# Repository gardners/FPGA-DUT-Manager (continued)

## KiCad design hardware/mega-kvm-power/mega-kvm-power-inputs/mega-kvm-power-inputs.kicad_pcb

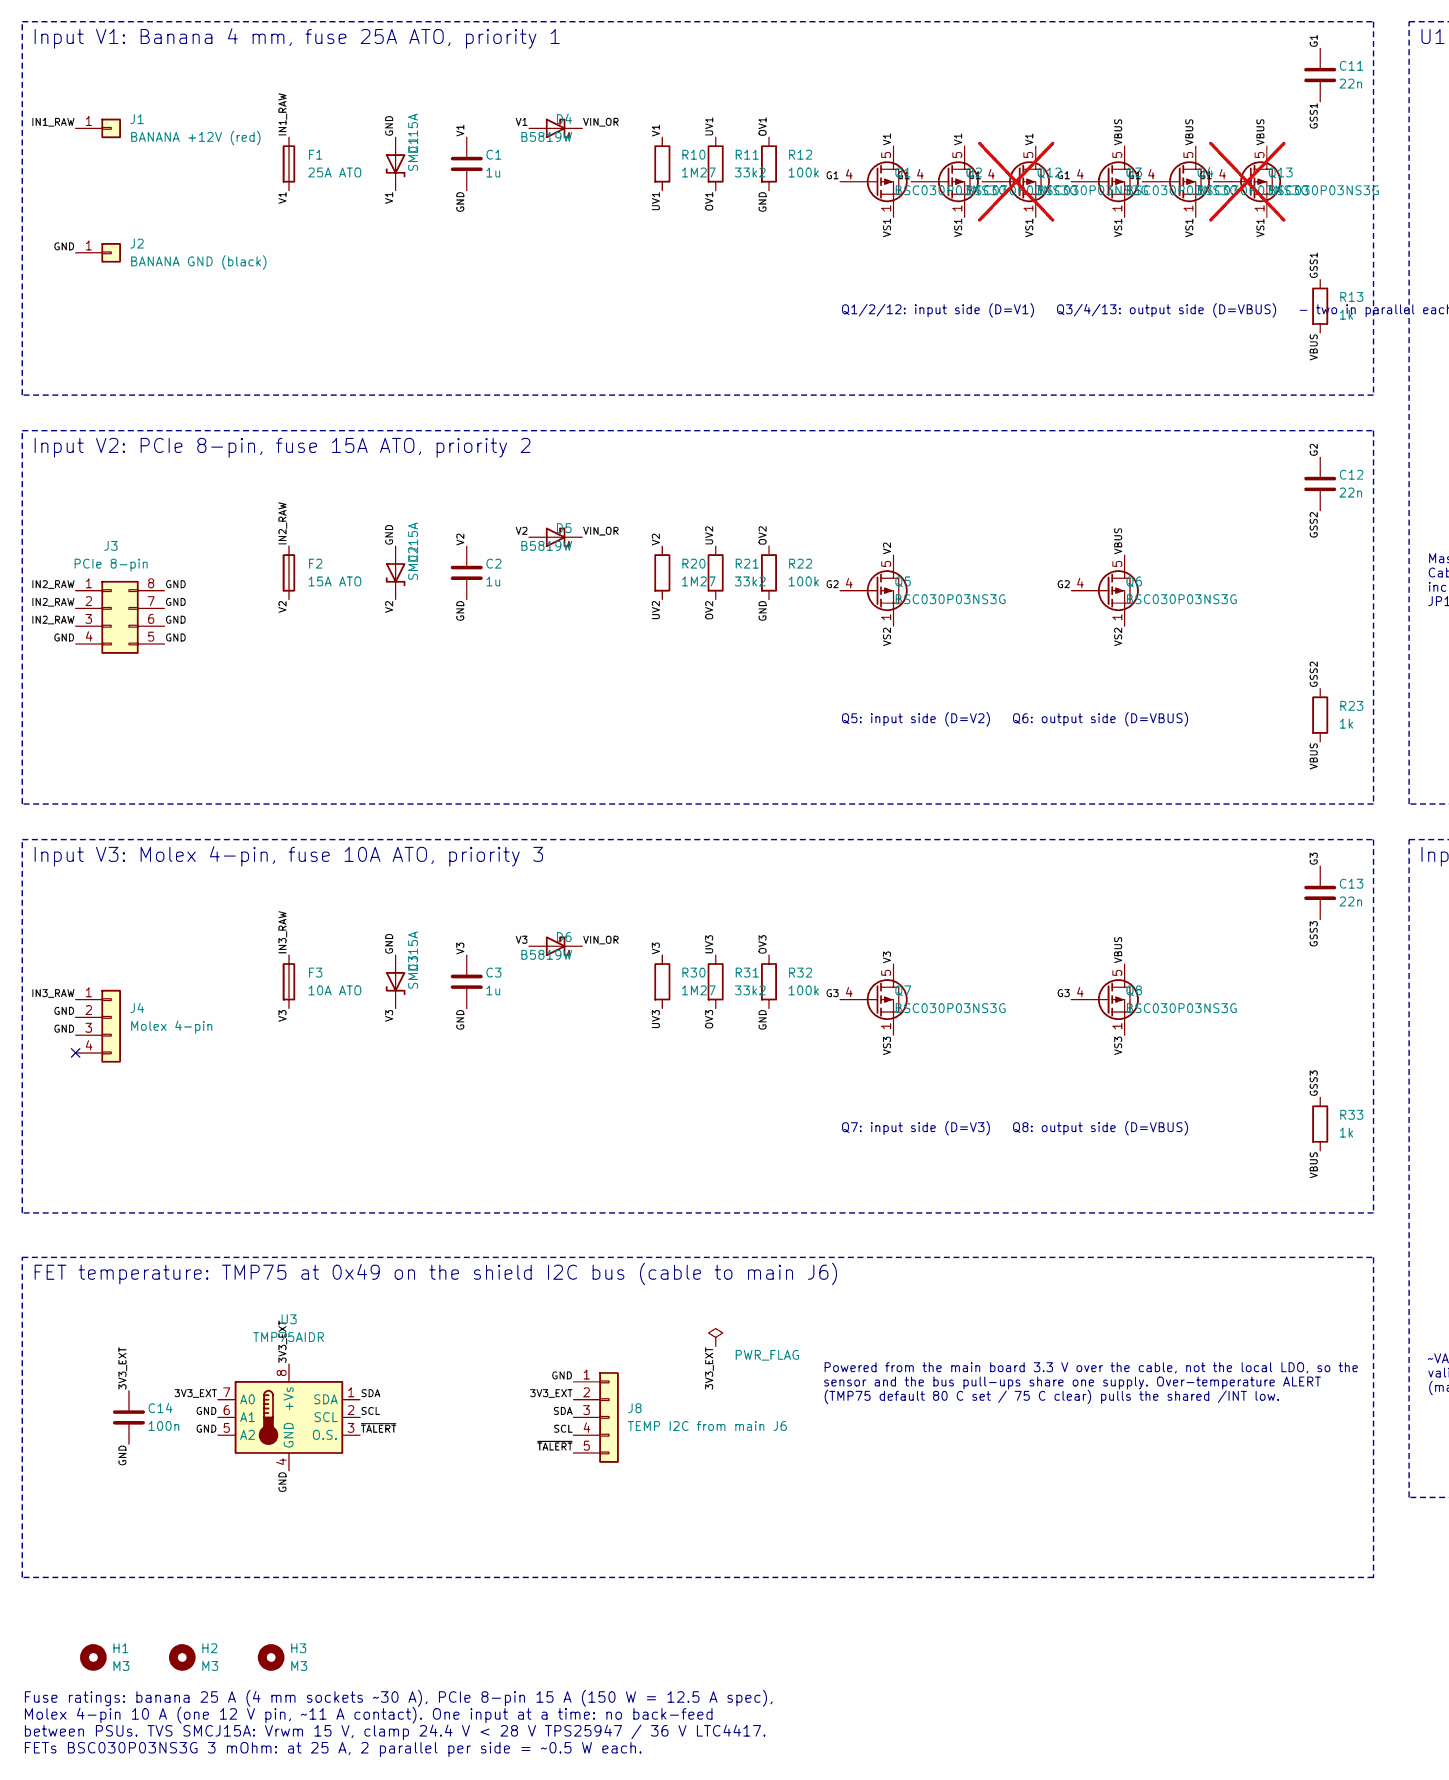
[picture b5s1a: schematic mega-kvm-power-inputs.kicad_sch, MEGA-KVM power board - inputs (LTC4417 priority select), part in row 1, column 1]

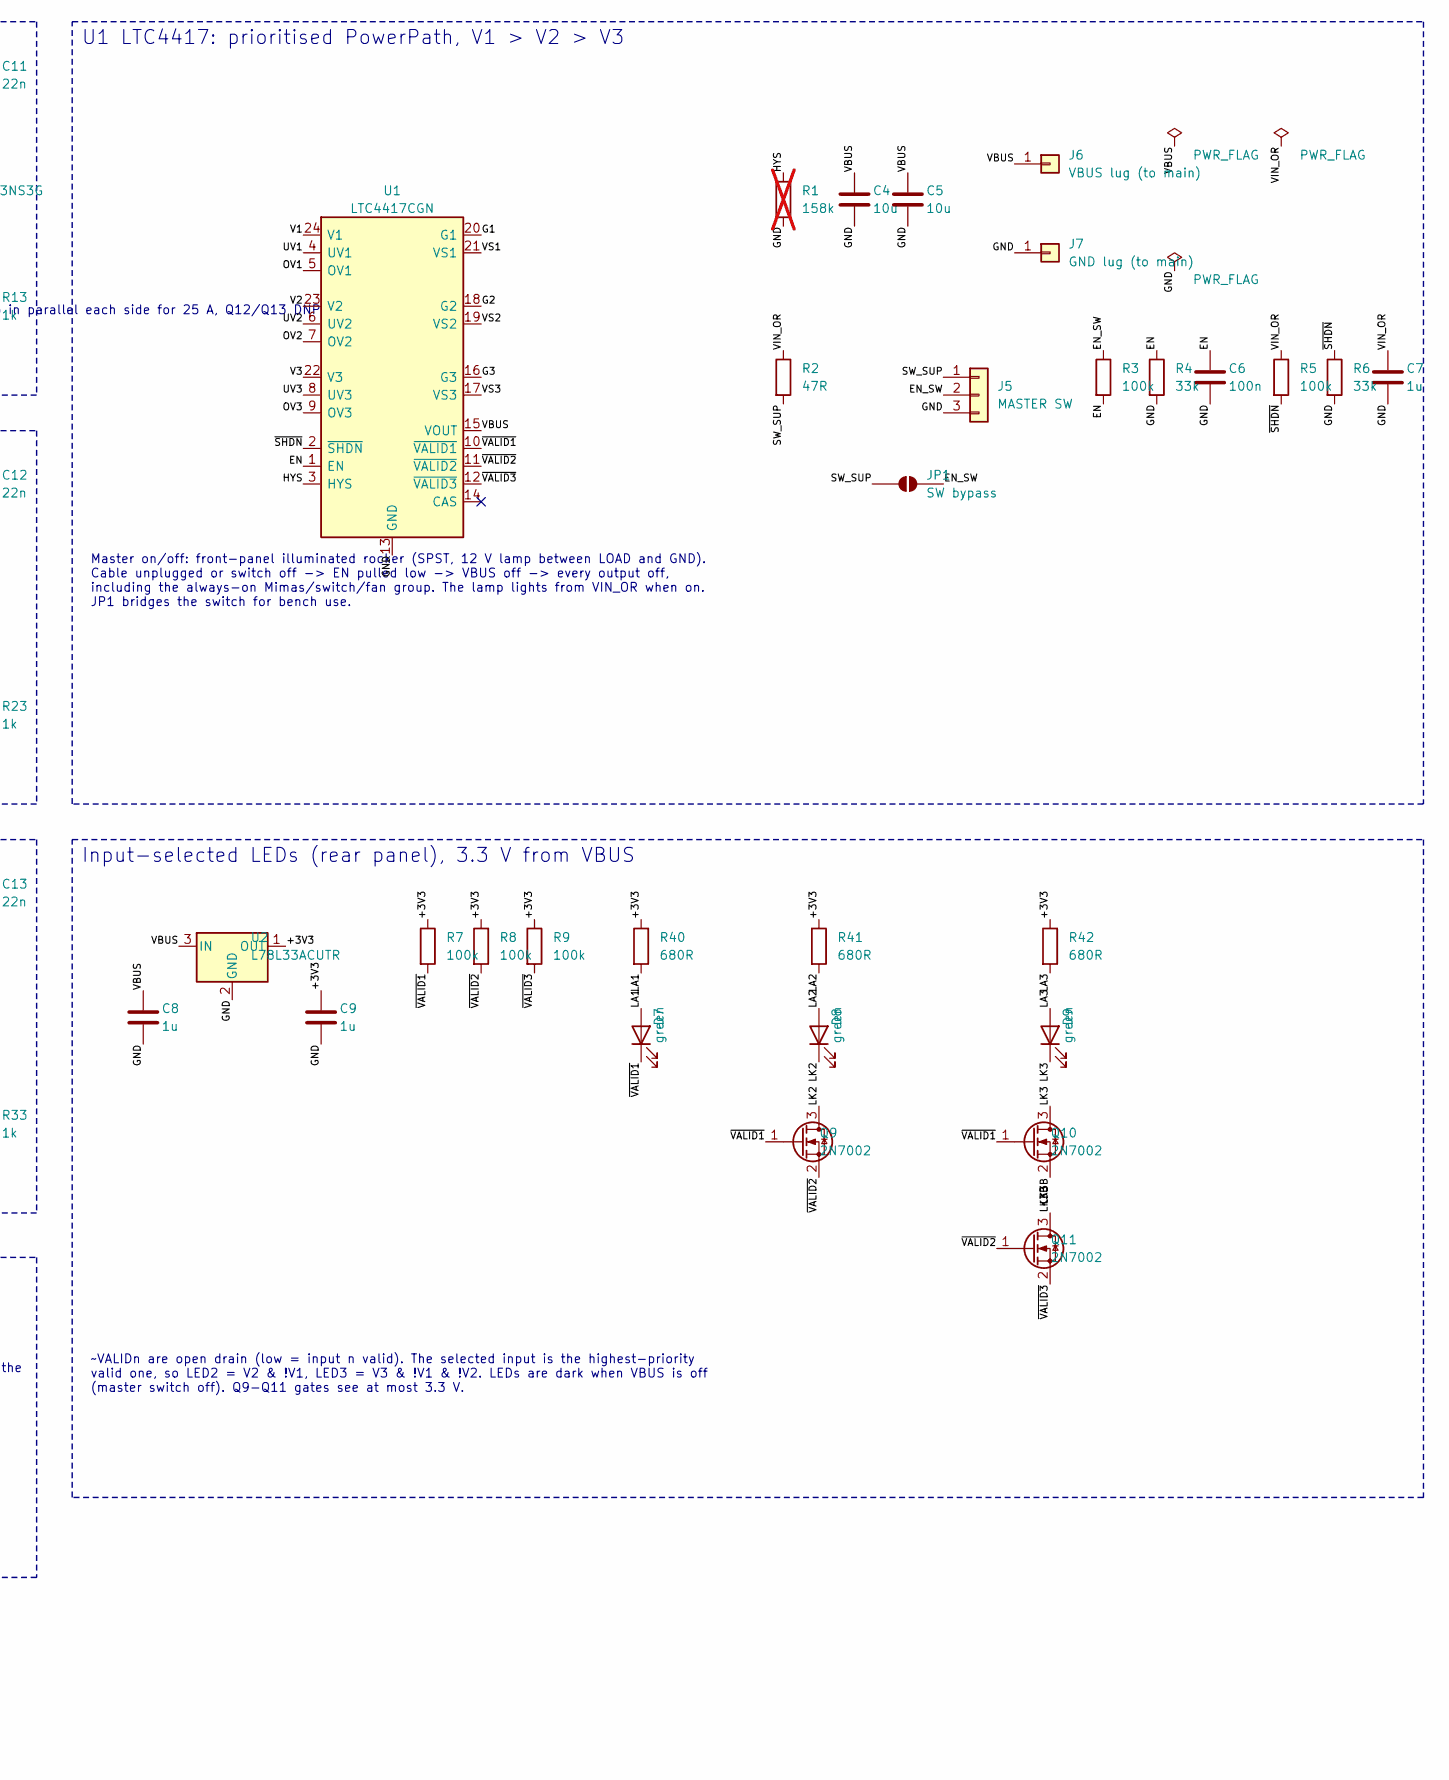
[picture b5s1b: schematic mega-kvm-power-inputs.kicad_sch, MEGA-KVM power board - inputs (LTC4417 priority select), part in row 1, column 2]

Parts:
C1, C2, C3: 1u; C_1206_3216Metric; Voltage 50V; LCSC TBD (X7R 50V)
C4, C5: 10u; C_1206_3216Metric; Voltage 25V; LCSC TBD (X7R 25V)
C6, C14: 100n; C_0603_1608Metric; Voltage 25V; LCSC C14663
C7, C8: 1u; C_0603_1608Metric; Voltage 50V; LCSC TBD (X7R 50V)
C9: 1u; C_0603_1608Metric; Voltage 16V; LCSC TBD (X7R 16V)
C11, C12, C13: 22n; C_0603_1608Metric; Voltage 50V; LCSC TBD (X7R 50V)
D1, D2, D3: SMCJ15A; D_SMC; MPN MDD SMCJ15A 1500 W, Vrwm 15 V, Vc 24.4 V; LCSC C2834490
D4, D5, D6: B5819W; D_SOD-123; MPN B5819W 40 V 1 A SOD-123; LCSC C8598
D7, D8, D9: green; LED_0603_1608Metric; LCSC TBD (0603 green, JLC basic)
F1: 25A ATO; FuseHolder_Blade_ATO_Littelfuse_FLR_178.6165; MPN Littelfuse 178.6165.0002 ATO PCB holder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; LCSC TBD / hand-fit
F2: 15A ATO; FuseHolder_Blade_ATO_Littelfuse_FLR_178.6165; MPN Littelfuse 178.6165.0002 ATO PCB holder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; LCSC TBD / hand-fit
F3: 10A ATO; FuseHolder_Blade_ATO_Littelfuse_FLR_178.6165; MPN Littelfuse 178.6165.0002 ATO PCB holder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; LCSC TBD / hand-fit
H1, H2, H3: M3; MountingHole_3.2mm_M3
J1: BANANA +12V (red); Banana_Jack_1Pin; MPN 4 mm panel socket >=30 A, red, through-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; LCSC hand-fit
J2: BANANA GND (black); Banana_Jack_1Pin; MPN 4 mm panel socket >=30 A, black; LCSC hand-fit
J3: PCIe 8-pin; Molex_Mini-Fit_Jr_5566-08A_2x04_P4.20mm_Vertical; MPN Molex Mini-Fit Jr 8-pin vertical header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; LCSC TBD / hand-fit
J4: Molex 4-pin; Molex_8981_PeripheralPower_1x04_P5.08mm_Vertical; MPN Molex 8981 4-pin male PCB header, verti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; LCSC TBD / hand-fit
J5: MASTER SW; JST_XH_B3B-XH-A_1x03_P2.50mm_Vertical; MPN JST B3B-XH-A; LCSC C144395 (verify)
J6: VBUS lug (to main); MountingHole_4.3mm_M4_Pad_Via; LCSC n/a (ring terminal + M4 screw/nut)
J7: GND lug (to main); MountingHole_4.3mm_M4_Pad_Via; LCSC n/a (ring terminal + M4 screw/nut)
J8: TEMP I2C from main J6; JST_XH_B5B-XH-A_1x05_P2.50mm_Vertical; MPN JST B5B-XH-A(LF)(SN); LCSC C157991
JP1: SW bypass; SolderJumper-2_P1.3mm_Open_RoundedPad1.0x1.5mm
Q1, Q2, Q3, Q4, Q5, Q6, Q7, Q8: BSC030P03NS3G; Infineon_PG-TDSON-8_6.15x5.15mm; MPN Infineon BSC030P03NS3G -30 V 3 mOhm; LCSC C152375
Q9, Q10, Q11: 2N7002; SOT-23; LCSC C8545
Q12, Q13: BSC030P03NS3G; Infineon_PG-TDSON-8_6.15x5.15mm; MPN Infineon BSC030P03NS3G -30 V 3 mOhm; LCSC C152375; not fitted
R1: 158k; R_0603_1608Metric; Tolerance 1%; LCSC TBD (1%, JLC basic if stocked); not fitted
R2: 47R; R_1206_3216Metric; Tolerance 1%; LCSC TBD (1%, JLC basic if stocked)
R3, R5, R7, R8, R9, R12, R22, R32: 100k; R_0603_1608Metric; Tolerance 1%; LCSC C25803
R4, R6: 33k; R_0603_1608Metric; Tolerance 1%; LCSC TBD (1%, JLC basic if stocked)
R10, R20, R30: 1M27; R_0603_1608Metric; Tolerance 1%; LCSC TBD (1%, JLC basic if stocked)
R11, R21, R31: 33k2; R_0603_1608Metric; Tolerance 1%; LCSC TBD (1%, JLC basic if stocked)
R13, R23, R33: 1k; R_0603_1608Metric; Tolerance 1%; LCSC C21190
R40, R41, R42: 680R; R_0603_1608Metric; Tolerance 1%; LCSC TBD (1%, JLC basic if stocked)
U1: LTC4417CGN; SSOP-24_3.9x8.7mm_P0.635mm; MPN ADI LTC4417CGN#PBF; LCSC C688500 (low stock: order via JLC globa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
U2: L78L33ACUTR; SOT-89-3; MPN ST L78L33ACUTR; LCSC TBD (78L33 SOT-89, 30 V in)
U3: TMP75AIDR; SOIC-8_3.9x4.9mm_P1.27mm; MPN TI TMP75AIDR (LM75 pinout, 0x48-0x4F), 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; LCSC C30389

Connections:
/3V3_EXT: C14.1, J8.2, U3.7 (A0), U3.8 (+Vs)
/+3V3: C9.1, R7.1, R8.1, R9.1, R40.1, R41.1, R42.1, U2.1 (OUT)
/EN: C6.1, R3.2, R4.1, U1.1 (EN)
/EN_SW: J5.2, JP1.2 (B), R3.1
/G1: C11.1, Q1.4 (G), Q2.4 (G), Q3.4 (G), Q4.4 (G), Q12.4 (G), Q13.4 (G), U1.20 (G1)
/G2: C12.1, Q5.4 (G), Q6.4 (G), U1.18 (G2)
/G3: C13.1, Q7.4 (G), Q8.4 (G), U1.16 (G3)
/GND: C1.2, C2.2, C3.2, C4.2, C5.2, C6.2, C7.2, C8.2, C9.2, C14.2, D1.2 (A), D2.2 (A), D3.2 (A), J2.1, J3.4, J3.5, J3.6, J3.7, J3.8, J4.2, J4.3, J5.3, J7.1, J8.1, R1.2, R4.2, R6.2, R12.2, R22.2, R32.2, U1.13 (GND), U2.2 (GND), U3.4 (GND), U3.5 (A2), U3.6 (A1)
/GSS1: C11.2, R13.1
/GSS2: C12.2, R23.1
/GSS3: C13.2, R33.1
/HYS: R1.1, U1.3 (HYS)
/IN1_RAW: F1.1, J1.1
/IN2_RAW: F2.1, J3.1, J3.2, J3.3
/IN3_RAW: F3.1, J4.1
/LA1: D7.2 (A), R40.2
/LA2: D8.2 (A), R41.2
/LA3: D9.2 (A), R42.2
/LK2: D8.1 (K), Q9.3 (D)
/LK3: D9.1 (K), Q10.3 (D)
/LK3B: Q10.2 (S), Q11.3 (D)
/OV1: R11.2, R12.1, U1.5 (OV1)
/OV2: R21.2, R22.1, U1.7 (OV2)
/OV3: R31.2, R32.1, U1.9 (OV3)
/SCL: J8.4, U3.2 (SCL)
/SDA: J8.3, U3.1 (SDA)
/SW_SUP: J5.1, JP1.1 (A), R2.2
/UV1: R10.2, R11.1, U1.4 (UV1)
/UV2: R20.2, R21.1, U1.6 (UV2)
/UV3: R30.2, R31.1, U1.8 (UV3)
/V1: C1.1, D1.1 (K), D4.2 (A), F1.2, Q1.5 (D), Q2.5 (D), Q12.5 (D), R10.1, U1.24 (V1)
/V2: C2.1, D2.1 (K), D5.2 (A), F2.2, Q5.5 (D), R20.1, U1.23 (V2)
/V3: C3.1, D3.1 (K), D6.2 (A), F3.2, Q7.5 (D), R30.1, U1.22 (V3)
/VBUS: C4.1, C5.1, C8.1, J6.1, Q3.5 (D), Q4.5 (D), Q6.5 (D), Q8.5 (D), Q13.5 (D), R13.2, R23.2, R33.2, U1.15 (VOUT), U2.3 (IN)
/VIN_OR: C7.1, D4.1 (K), D5.1 (K), D6.1 (K), R2.1, R5.1
/VS1: Q1.1 (S), Q1.2 (S), Q1.3 (S), Q2.1 (S), Q2.2 (S), Q2.3 (S), Q3.1 (S), Q3.2 (S), Q3.3 (S), Q4.1 (S), Q4.2 (S), Q4.3 (S), Q12.1 (S), Q12.2 (S), Q12.3 (S), Q13.1 (S), Q13.2 (S), Q13.3 (S), U1.21 (VS1)
/VS2: Q5.1 (S), Q5.2 (S), Q5.3 (S), Q6.1 (S), Q6.2 (S), Q6.3 (S), U1.19 (VS2)
/VS3: Q7.1 (S), Q7.2 (S), Q7.3 (S), Q8.1 (S), Q8.2 (S), Q8.3 (S), U1.17 (VS3)
/~SHDN: R5.2, R6.1, U1.2 (~SHDN)
/~TALERT: J8.5, U3.3 (O.S.)
/~VALID1: D7.1 (K), Q9.1 (G), Q10.1 (G), R7.2, U1.10 (~VALID1)
/~VALID2: Q9.2 (S), Q11.1 (G), R8.2, U1.11 (~VALID2)
/~VALID3: Q11.2 (S), R9.2, U1.12 (~VALID3)

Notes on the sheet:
Input V1: Banana 4 mm, fuse 25A ATO, priority 1
Q1/2/12: input side (D=V1) Q3/4/13: output side (D=VBUS) - two in parallel each side for 25 A, Q12/Q13 DNP
Input V2: PCIe 8-pin, fuse 15A ATO, priority 2
Q5: input side (D=V2) Q6: output side (D=VBUS)
Input V3: Molex 4-pin, fuse 10A ATO, priority 3
Q7: input side (D=V3) Q8: output side (D=VBUS)
U1 LTC4417: prioritised PowerPath, V1 > V2 > V3
Master on/off: front-panel illuminated rocker (SPST, 12 V lamp between LOAD and GND). Cable unplugged or switch off -> EN pulled low -> VBUS off -> every output off, including the always-on Mimas/switch/fan group. The lamp lights from VIN_OR when on. JP1 bridges the switch for bench use.
Input-selected LEDs (rear panel), 3.3 V from VBUS
~VALIDn are open drain (low = input n valid). The selected input is the highest-priority valid one, so LED2 = V2 & !V1, LED3 = V3 & !V1 & !V2. LEDs are dark when VBUS is off (master switch off). Q9-Q11 gates see at most 3.3 V.
FET temperature: TMP75 at 0x49 on the shield I2C bus (cable to main J6)
Powered from the main board 3.3 V over the cable, not the local LDO, so the sensor and the bus pull-ups share one supply. Over-temperature ALERT (TMP75 default 80 C set / 75 C clear) pulls the shared /INT low.
Fuse ratings: banana 25 A (4 mm sockets ~30 A), PCIe 8-pin 15 A (150 W = 12.5 A spec), Molex 4-pin 10 A (one 12 V pin, ~11 A contact). One input at a time: no back-feed between PSUs. TVS SMCJ15A: Vrwm 15 V, clamp 24.4 V < 28 V TPS25947 / 36 V LTC4417. FETs BSC030P03NS3G 3 mOhm: at 25 A, 2 parallel 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

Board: 2 copper layers, 77 parts (65 on the bottom side), 43 nets, no tracks yet.

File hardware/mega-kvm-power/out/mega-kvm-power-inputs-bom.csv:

"Refs","Value","Footprint","LCSC","MPN","Qty","DNP"
"C1,C2,C3","1u","Capacitor_SMD:C_1206_3216Metric","TBD (X7R 50V)","","3",""
"C4,C5","10u","Capacitor_SMD:C_1206_3216Metric","TBD (X7R 25V)","","2",""
"C6,C14","100n","Capacitor_SMD:C_0603_1608Metric","C14663","","2",""
"C7,C8","1u","Capacitor_SMD:C_0603_1608Metric","TBD (X7R 50V)","","2",""
"C9","1u","Capacitor_SMD:C_0603_1608Metric","TBD (X7R 16V)","","1",""
"C11,C12,C13","22n","Capacitor_SMD:C_0603_1608Metric","TBD (X7R 50V)","","3",""
"D1,D2,D3","SMCJ15A","Diode_SMD:D_SMC","C2834490","MDD SMCJ15A 1500 W, Vrwm 15 V, Vc 24.4 V","3",""
"D4,D5,D6","B5819W","Diode_SMD:D_SOD-123","C8598","B5819W 40 V 1 A SOD-123","3",""
"D7,D8,D9","green","LED_SMD:LED_0603_1608Metric","TBD (0603 green, JLC basic)","","3",""
"F1","25A ATO","Fuse:FuseHolder_Blade_ATO_Littelfuse_FLR_178.6165","TBD / hand-fit","Littelfuse 178.6165.0002 ATO PCB holder + ATO blade fuse 25A ATO","1",""
"F2","15A ATO","Fuse:FuseHolder_Blade_ATO_Littelfuse_FLR_178.6165","TBD / hand-fit","Littelfuse 178.6165.0002 ATO PCB holder + ATO blade fuse 15A ATO","1",""
"F3","10A ATO","Fuse:FuseHolder_Blade_ATO_Littelfuse_FLR_178.6165","TBD / hand-fit","Littelfuse 178.6165.0002 ATO PCB holder + ATO blade fuse 10A ATO","1",""
"J1","BANANA +12V (red)","Connector:Banana_Jack_1Pin","hand-fit","4 mm panel socket >=30 A, red, through-PCB with nut + solder lug (e.g. Staubli/Multi-Contact or Cliff, choose at order)","1",""
"J2","BANANA GND (black)","Connector:Banana_Jack_1Pin","hand-fit","4 mm panel socket >=30 A, black","1",""
"J3","PCIe 8-pin","Connector_Molex:Molex_Mini-Fit_Jr_5566-08A_2x04_P4.20mm_Vertical","TBD / hand-fit","Molex Mini-Fit Jr 8-pin vertical header with PCIe keying (45558-series or 39-28-1083 + check keying); pins 1-3 +12 V, 4-8 GND (sense pins grounded)","1",""
"J4","Molex 4-pin","mega-kvm-power:Molex_8981_PeripheralPower_1x04_P5.08mm_Vertical","TBD / hand-fit","Molex 8981 4-pin male PCB header, vertical (e.g. 15-24-4048); 1 +12 V, 2-3 GND, 4 +5 V unused","1",""
"J5","MASTER SW","Connector_JST:JST_XH_B3B-XH-A_1x03_P2.50mm_Vertical","C144395 (verify)","JST B3B-XH-A","1",""
"J8","TEMP I2C from main J6","Connector_JST:JST_XH_B5B-XH-A_1x05_P2.50mm_Vertical","C157991","JST B5B-XH-A(LF)(SN)","1",""
"Q1,Q2,Q3,Q4,Q5,Q6,Q7,Q8","BSC030P03NS3G","Package_SON:Infineon_PG-TDSON-8_6.15x5.15mm","C152375","Infineon BSC030P03NS3G -30 V 3 mOhm","8",""
"Q9,Q10,Q11","2N7002","Package_TO_SOT_SMD:SOT-23","C8545","","3",""
"Q12,Q13","BSC030P03NS3G","Package_SON:Infineon_PG-TDSON-8_6.15x5.15mm","C152375","Infineon BSC030P03NS3G -30 V 3 mOhm","2","DNP"
"R1","158k","Resistor_SMD:R_0603_1608Metric","TBD (1%, JLC basic if stocked)","","1","DNP"
"R2","47R","Resistor_SMD:R_1206_3216Metric","TBD (1%, JLC basic if stocked)","","1",""
"R3,R5,R7,R8,R9,R12,R22,R32","100k","Resistor_SMD:R_0603_1608Metric","C25803","","8",""
"R4,R6","33k","Resistor_SMD:R_0603_1608Metric","TBD (1%, JLC basic if stocked)","","2",""
"R10,R20,R30","1M27","Resistor_SMD:R_0603_1608Metric","TBD (1%, JLC basic if stocked)","","3",""
"R11,R21,R31","33k2","Resistor_SMD:R_0603_1608Metric","TBD (1%, JLC basic if stocked)","","3",""
"R13,R23,R33","1k","Resistor_SMD:R_0603_1608Metric","C21190","","3",""
"R40,R41,R42","680R","Resistor_SMD:R_0603_1608Metric","TBD (1%, JLC basic if stocked)","","3",""
"U1","LTC4417CGN","Package_SO:SSOP-24_3.9x8.7mm_P0.635mm","C688500 (low stock: order via JLC global sourcing / parts pre-order; SSOP-24, no exposed pad)","ADI LTC4417CGN#PBF","1",""
"U2","L78L33ACUTR","Package_TO_SOT_SMD:SOT-89-3","TBD (78L33 SOT-89, 30 V in)","ST L78L33ACUTR","1",""
"U3","TMP75AIDR","Package_SO:SOIC-8_3.9x4.9mm_P1.27mm","C30389","TI TMP75AIDR (LM75 pinout, 0x48-0x4F), SOIC-8","1",""

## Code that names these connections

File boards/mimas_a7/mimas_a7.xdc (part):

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set_property -dict {PACKAGE_PIN Y22 IOSTANDARD LVCMOS33} [get_ports usb_uart_rx]
set_property -dict {PACKAGE_PIN Y21 IOSTANDARD LVCMOS33} [get_ports usb_uart_tx]

## Neighbour link (issue 0069, ADR 0007 point 2; shield pin plan NB_UART_TX /
## NB_UART_RX): crossover UART to the unit's other supervisor on P12 row 23
## (A = G17 GPIO_14_P TX out, B = G18 GPIO_14_N RX in; GND on row 24). Same
## pins in the normal and the shield build. Board-to-board only (both boards
## are powered together), so TX is always driven (idle high); the RX PULLUP
## makes an open link read idle.
set_property -dict {PACKAGE_PIN G17 IOSTANDARD LVCMOS33 DRIVE 8 SLEW SLOW} [get_ports nb_uart_tx]
set_property -dict {PACKAGE_PIN G18 IOSTANDARD LVCMOS33 PULLUP TRUE} [get_ports nb_uart_rx]

## LEDs, DIP switch, push buttons
set_property -dict {PACKAGE_PIN K17 IOSTANDARD LVCMOS33} [get_ports {led[0]}]
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##               J5 pin 2 (3V3) by its own jumper to row 22 A (sense input)
## No pulls on signals (brief section 5: minimise back-powering); sense inputs
## have PULLDOWN so an unplugged DUT reads unpowered. SLOW slew, 8 mA.
set_property -dict {PACKAGE_PIN J21 IOSTANDARD LVCMOS33} [get_ports dut0_uart_from]
set_property -dict {PACKAGE_PIN J20 IOSTANDARD LVCMOS33 DRIVE 8 SLEW SLOW} [get_ports dut0_tck]
set_property -dict {PACKAGE_PIN K22 IOSTANDARD LVCMOS33 DRIVE 8 SLEW SLOW} [get_ports dut0_uart_to]
set_property -dict {PACKAGE_PIN K21 IOSTANDARD LVCMOS33} [get_ports dut0_tdo]
set_property -dict {PACKAGE_PIN G20 IOSTANDARD LVCMOS33 PULLDOWN TRUE} [get_ports dut0_vio_sense]
set_property -dict {PACKAGE_PIN H20 IOSTANDARD LVCMOS33 DRIVE 8 SLEW SLOW} [get_ports dut0_tdi]
set_property -dict {PACKAGE_PIN J19 IOSTANDARD LVCMOS33 DRIVE 8 SLEW SLOW} [get_ports dut0_tms]
set_property -dict {PACKAGE_PIN N20 IOSTANDARD LVCMOS33} [get_ports dut0_kio8]
set_property -dict {PACKAGE_PIN M22 IOSTANDARD LVCMOS33} [get_ports dut0_kio9]
set_property -dict {PACKAGE_PIN N22 IOSTANDARD LVCMOS33 DRIVE 8 SLEW SLOW} [get_ports dut0_kio10]
set_property -dict {PACKAGE_PIN H17 IOSTANDARD LVCMOS33 PULLDOWN TRUE} [get_ports dut0_kb_sense]

set_property -dict {PACKAGE_PIN F20 IOSTANDARD LVCMOS33} [get_ports dut1_uart_from]
set_property -dict {PACKAGE_PIN F19 IOSTANDARD LVCMOS33 DRIVE 8 SLEW SLOW} [get_ports dut1_tck]
set_property -dict {PACKAGE_PIN D19 IOSTANDARD LVCMOS33 DRIVE 8 SLEW SLOW} [get_ports dut1_uart_to]
set_property -dict {PACKAGE_PIN E19 IOSTANDARD LVCMOS33} [get_ports dut1_tdo]
set_property -dict {PACKAGE_PIN C20 IOSTANDARD LVCMOS33 PULLDOWN TRUE} [get_ports dut1_vio_sense]
set_property -dict {PACKAGE_PIN D20 IOSTANDARD LVCMOS33 DRIVE 8 SLEW SLOW} [get_ports dut1_tdi]
set_property -dict {PACKAGE_PIN C22 IOSTANDARD LVCMOS33 DRIVE 8 SLEW SLOW} [get_ports dut1_tms]
set_property -dict {PACKAGE_PIN A18 IOSTANDARD LVCMOS33} [get_ports dut1_kio8]
set_property -dict {PACKAGE_PIN B18 IOSTANDARD LVCMOS33} [get_ports dut1_kio9]
set_property -dict {PACKAGE_PIN B17 IOSTANDARD LVCMOS33 DRIVE 8 SLEW SLOW} [get_ports dut1_kio10]
set_property -dict {PACKAGE_PIN A15 IOSTANDARD LVCMOS33 PULLDOWN TRUE} [get_ports dut1_kb_sense]

## HDMI OUT (bank 35, TMDS_33 via IP4776 buffer); text display, ADR 0012
set_property -dict {PACKAGE_PIN L3 IOSTANDARD TMDS_33} [get_ports hdmi_tx_clk_p]
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## detected by kbd_phys_host (issue 0009). The MK-II PCB has 1k pull-ups
## (R13/R14); the weak PULLUPs here only stop an empty port from floating
## (the keyboard is powered from the supervisor side, so no back-powering).
set_property -dict {PACKAGE_PIN K18 IOSTANDARD LVCMOS33 DRIVE 8 SLEW SLOW PULLUP TRUE} [get_ports pk_kio8]
set_property -dict {PACKAGE_PIN H22 IOSTANDARD LVCMOS33 DRIVE 8 SLEW SLOW PULLUP TRUE} [get_ports pk_kio9]
set_property -dict {PACKAGE_PIN J22 IOSTANDARD LVCMOS33 PULLDOWN TRUE} [get_ports pk_kio10]

## Physical keyboard CPLD JTAG (issue 0046, ADR 0014): pins depend on the
## build, so they are not here: pk_jtag_bodge.xdc (normal build, the J5
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
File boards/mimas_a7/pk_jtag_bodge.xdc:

# Physical keyboard CPLD JTAG, normal (bodge) build: read by vivado/build.tcl
# only when SHIELD_RX = 0. pk_jtagen exists only in this build (in the shield
# build PK_JTAGEN is on I2C expander B).
## Physical keyboard CPLD JTAG (keyboard J5 pins 3-7 = P12 rows 13-11B,
## issue 0046, ADR 0014): a third JTAG engine (JTAG_REQ flags b1), tri-
## stated unless enabled (keyboard detected / lease / MGMT key 0x0061).
## Row r = GPIO_(r-5) for rows 10-13; column A = _P, column B = _N.
##   row 13 B L21 GPIO_8_N KB_JTAGEN (pin 3, driven '1' when enabled)
##   row 13 A M21 GPIO_8_P KB_TMS    (pin 4)
##   row 12 B L20 GPIO_7_N KB_TCK    (pin 5)
##   row 12 A L19 GPIO_7_P KB_TDI    (pin 6)
##   row 11 B K19 GPIO_6_N KB_TDO    (pin 7, input)
## Normal (bodge) build only: the shield build gives L19/L20/M21/L21 to
## HDMI3 and uses its own keyboard JTAG pins (shield_v1.xdc). Weak pulls hold
## the TAP quiet while tri-stated: TCK and JTAGEN low (the MEGA65 mainboard
## also holds kb_jtagen low), TMS high (TAP stays in Test-Logic-Reset).
set_property -dict {PACKAGE_PIN L21 IOSTANDARD LVCMOS33 DRIVE 8 SLEW SLOW PULLDOWN TRUE} [get_ports {pk_jtagen[0]}]
set_property -dict {PACKAGE_PIN M21 IOSTANDARD LVCMOS33 DRIVE 8 SLEW SLOW PULLUP TRUE}   [get_ports pk_tms]
set_property -dict {PACKAGE_PIN L20 IOSTANDARD LVCMOS33 DRIVE 8 SLEW SLOW PULLDOWN TRUE} [get_ports pk_tck]
set_property -dict {PACKAGE_PIN L19 IOSTANDARD LVCMOS33 DRIVE 8 SLEW SLOW PULLUP TRUE}   [get_ports pk_tdi]
set_property -dict {PACKAGE_PIN K19 IOSTANDARD LVCMOS33 PULLUP TRUE} [get_ports pk_tdo]
set_false_path -to   [get_ports {pk_jtagen[*] pk_tck pk_tms pk_tdi}]
set_false_path -from [get_ports pk_tdo]
